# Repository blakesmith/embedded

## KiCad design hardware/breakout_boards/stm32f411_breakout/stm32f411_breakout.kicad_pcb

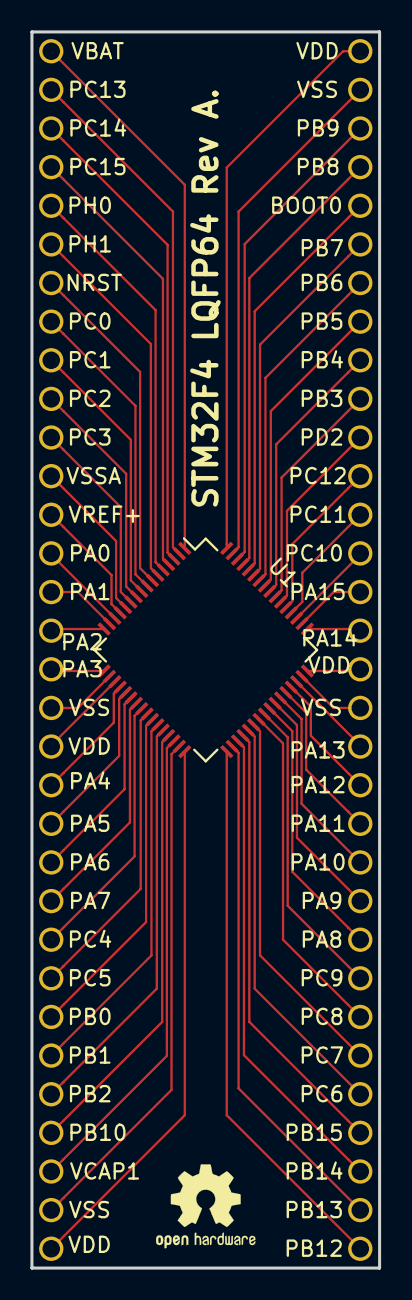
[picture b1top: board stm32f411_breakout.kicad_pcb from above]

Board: 2 copper layers, 22.9 x 81.3 mm, 65 parts (0 on the bottom side), 63 nets.

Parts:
BOOT0: Conn; Conn_1pin_2.54mm
NRST: Conn; Conn_1pin_2.54mm
PA0, PA1, PA2, PA3, PA4, PA5, PA6, PA7, PA8, PA9, PA10, PA11, PA12, PA13, PA14, PA15: Conn; Conn_1pin_2.54mm
PB0, PB1, PB2, PB3, PB4, PB5, PB6, PB7, PB8, PB9, PB10, PB12, PB13, PB14, PB15: Conn; Conn_1pin_2.54mm
PC0, PC1, PC2, PC3, PC4, PC5, PC6, PC7, PC8, PC9, PC10, PC11, PC12, PC13, PC14, PC15: Conn; Conn_1pin_2.54mm
PD2: Conn; Conn_1pin_2.54mm
PH0, PH1: Conn; Conn_1pin_2.54mm
U1: STM32F411RETx; LQFP-64_10x10mm_Pitch0.5mm
VBAT: Conn; Conn_1pin_2.54mm
VCAP1: Conn; Conn_1pin_2.54mm
VDD: Conn; Conn_1pin_2.54mm
VDD#2, VDD#3, VDD#4: Conn; Conn_1pin_2.54mm
VREF+: Conn; Conn_1pin_2.54mm
VSS: Conn; Conn_1pin_2.54mm
VSS#2, VSS#3, VSS#4: Conn; Conn_1pin_2.54mm
VSSA: Conn; Conn_1pin_2.54mm

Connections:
unnamed: NRST.1, U1.7
unnamed: BOOT0.1, U1.60
unnamed: U1.1, VBAT.1
unnamed: U1.13, VREF+.1
unnamed: U1.30, VCAP1.1
unnamed: PH0.1, U1.5
unnamed: PH1.1, U1.6
unnamed: PD2.1, U1.54
unnamed: PC0.1, U1.8
unnamed: PC1.1, U1.9
unnamed: PC2.1, U1.10
unnamed: PC3.1, U1.11
unnamed: PC4.1, U1.24
unnamed: PC5.1, U1.25
unnamed: PC6.1, U1.37
unnamed: PC7.1, U1.38
unnamed: PC8.1, U1.39
unnamed: PC9.1, U1.40
unnamed: PC10.1, U1.51
unnamed: PC11.1, U1.52
unnamed: PC12.1, U1.53
unnamed: PC13.1, U1.2
unnamed: PC15.1, U1.4
unnamed: U1.19, VDD.1
unnamed: U1.18, VSS.1
unnamed: U1.32, VDD#2.1
unnamed: U1.31, VSS#2.1
unnamed: U1.48, VDD#3.1
unnamed: U1.47, VSS#3.1
unnamed: U1.64, VDD#4.1
unnamed: U1.63, VSS#4.1
unnamed: U1.12, VSSA.1
unnamed: PA0.1, U1.14
unnamed: PA1.1, U1.15
unnamed: PA2.1, U1.16
unnamed: PA3.1, U1.17
unnamed: PA4.1, U1.20
unnamed: PA5.1, U1.21
unnamed: PA6.1, U1.22
unnamed: PA7.1, U1.23
unnamed: PA8.1, U1.41
unnamed: PA9.1, U1.42
unnamed: PA10.1, U1.43
unnamed: PA11.1, U1.44
unnamed: PA12.1, U1.45
unnamed: PA13.1, U1.46
unnamed: PA14.1, U1.49
unnamed: PA15.1, U1.50
unnamed: PB0.1, U1.26
unnamed: PB1.1, U1.27
unnamed: PB2.1, U1.28
unnamed: PB3.1, U1.55
unnamed: PB4.1, U1.56
unnamed: PB5.1, U1.57
unnamed: PB6.1, U1.58
unnamed: PB7.1, U1.59
unnamed: PB8.1, U1.61
unnamed: PB9.1, U1.62
unnamed: PB10.1, U1.29
unnamed: PB12.1, U1.33
unnamed: PB13.1, U1.34
unnamed: PB14.1, U1.35
unnamed: PB15.1, U1.36

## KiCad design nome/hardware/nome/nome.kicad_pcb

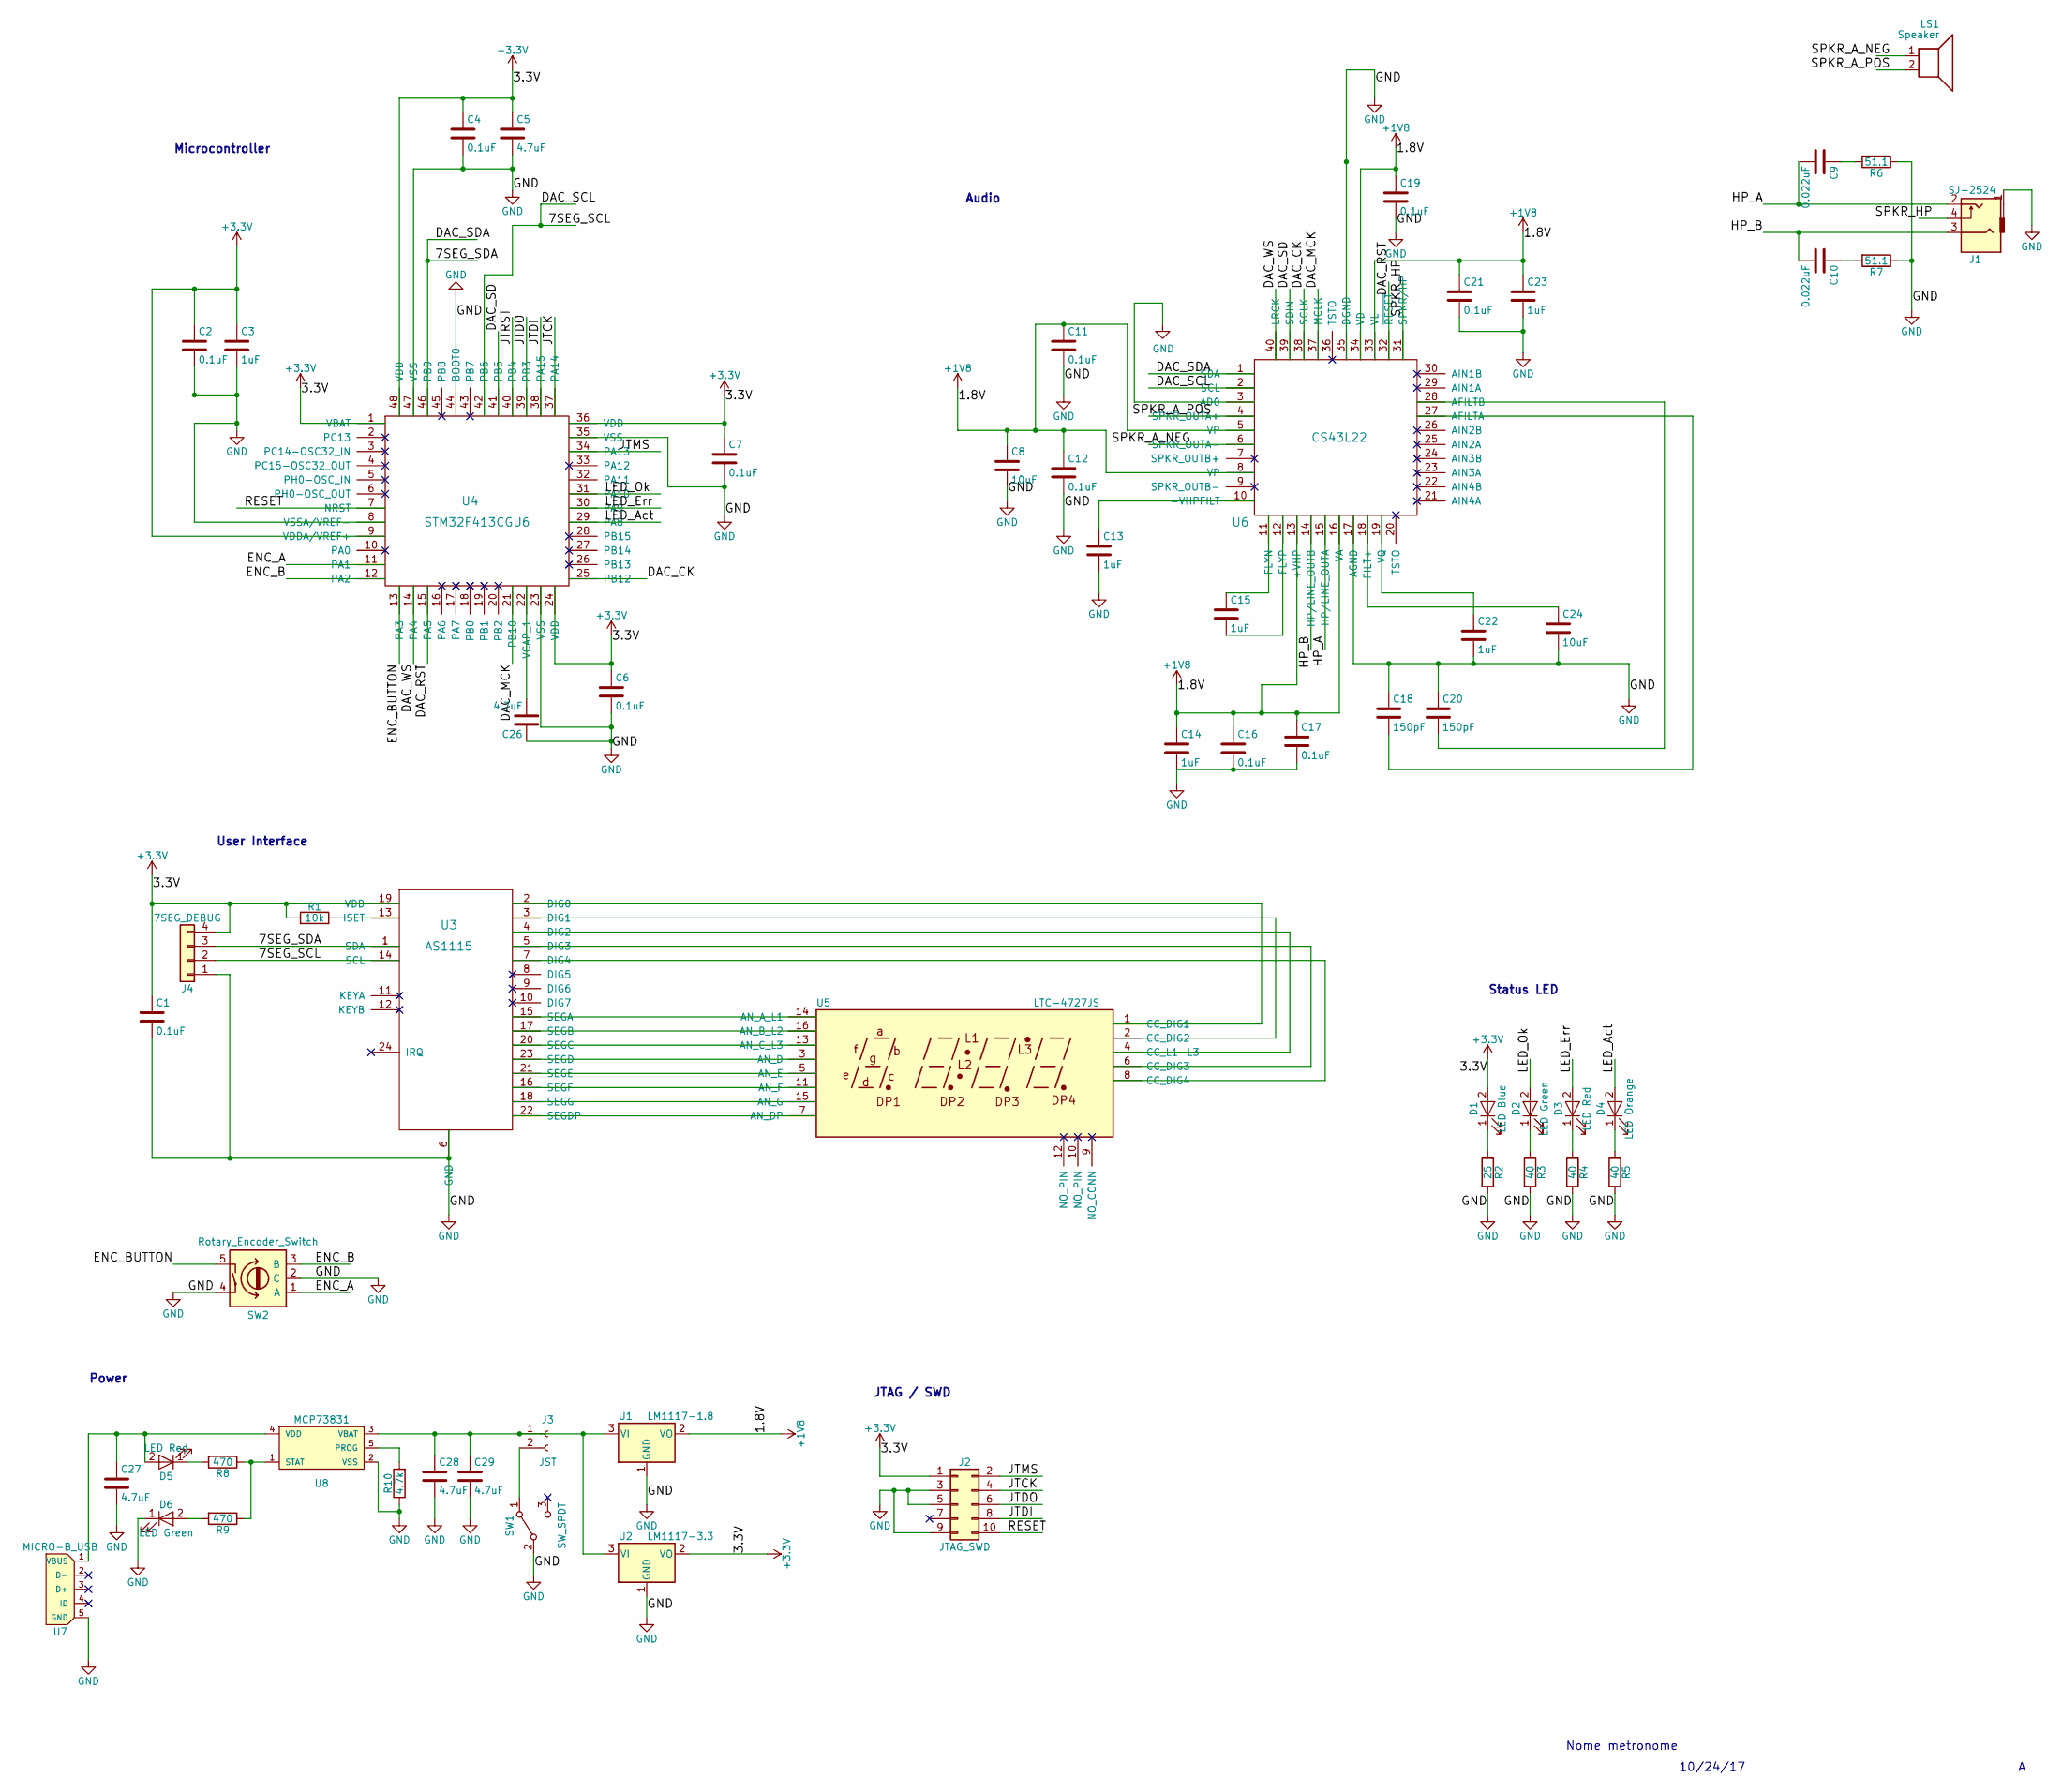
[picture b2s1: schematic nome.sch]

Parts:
C1, C2, C4, C6, C7, C11, C12, C16, C17, C19, C21: 0.1uF; C_0805_HandSoldering
C3, C13, C14, C15, C22, C23: 1uF; C_0805_HandSoldering
C5, C26, C27, C28, C29: 4.7uF; C_0805_HandSoldering
C8, C24: 10uF; C_0805_HandSoldering
C9, C10: 0.022uF; C_0805_HandSoldering
C18, C20: 150pF; C_0805_HandSoldering
D1: LED Blue; LED_0805_HandSoldering
D2, D6: LED Green; LED_0805_HandSoldering
D3, D5: LED Red; LED_0805_HandSoldering
D4: LED Orange; LED_0805_HandSoldering
J1: SJ-2524
J2: JTAG_SWD; Pin_Header_Straight_2x05_Pitch2.54mm
J3: JST; JST_PH_B2B-PH-SM4-TB_02x2.00mm_Straight
J4: 7SEG_DEBUG; Pin_Header_Straight_1x04_Pitch2.54mm
LS1: Speaker; WirePad-1x2-2.54mm
R1: 10k; R_0805_HandSoldering
R2: 25; R_0805_HandSoldering
R3, R4, R5: 40; R_0805_HandSoldering
R6, R7: 51.1; R_0805_HandSoldering
R8, R9: 470; R_0805_HandSoldering
R10: 4.7k; R_0805_HandSoldering
SW1: SW_SPDT; CK_SPDT
SW2: Rotary_Encoder_Switch; PEC11
U1: LM1117-1.8; SOT-223
U2: LM1117-3.3; SOT-223
U3: AS1115; QSOP-24_3.9x8.7mm_Pitch0.635mm
U4: STM32F413CGU6; LQFP-48_7x7mm_Pitch0.5mm
U5: LTC-4727JS; LTC-4727
U6: CS43L22; QFN-40-1EP_6x6mm_Pitch0.5mm
U7: MICRO-B_USB
U8: MCP73831; SOT-23-5_HandSoldering

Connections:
+1V8: C8.1, C11.1, C12.1, C14.1, C16.1, C17.1, C19.1, C21.1, C23.1, U1.2 (VO), U6.5 (VP), U6.8 (VP), U6.13 (+VHP), U6.16 (VA), U6.33 (VL), U6.34 (VD)
+3V3: C1.1, C2.1, C3.1, C4.1, C5.1, C6.1, C7.1, D1.2 (A), J2.1, J4.4, R1.1, U2.2 (VO), U3.19 (VDD), U4.1 (VBAT), U4.9 (VDDA/VREF+), U4.24 (VDD), U4.36 (VDD), U4.48 (VDD)
/7SEG_SCL: J4.2, U3.14 (SCL), U4.42 (PB6), U6.2 (SCL)
/7SEG_SDA: J4.3, U3.1 (SDA), U4.46 (PB9), U6.1 (SDA)
/DAC_CK: U4.25 (PB12), U6.38 (SCLK)
/DAC_MCK: U4.21 (PB10), U6.37 (MCLK)
/DAC_RST: U4.15 (PA5), U6.32 (~RESET)
/DAC_SD: U4.41 (PB5), U6.39 (SDIN)
/DAC_WS: U4.14 (PA4), U6.40 (LRCK)
/ENC_A: SW2.1 (A), U4.11 (PA1)
/ENC_B: SW2.3 (B), U4.12 (PA2)
/ENC_BUTTON: SW2.5, U4.13 (PA3)
/HP_A: C9.2, J1.2, U6.15 (HP/LINE_OUTA)
/HP_B: C10.2, J1.3, U6.14 (HP/LINE_OUTB)
/JTCK: J2.4, U4.37 (PA14)
/JTDI: J2.8, U4.38 (PA15)
/JTDO: J2.6, U4.39 (PB3)
/JTMS: J2.2, U4.34 (PA13)
/JTRST: U4.40 (PB4)
/LED_Act: D4.2 (A), U4.29 (PA8)
/LED_Err: D3.2 (A), U4.30 (PA9)
/LED_Ok: D2.2 (A), U4.31 (PA10)
/RESET: J2.10, U4.7 (NRST)
/SPKR_A_NEG: LS1.1, U6.6 (SPKR_OUTA-)
/SPKR_A_POS: LS1.2, U6.4 (SPKR_OUTA+)
/SPKR_HP: J1.4, U6.31 (SPKR/HP)
GND: C1.2, C2.2, C3.2, C4.2, C5.2, C6.2, C7.2, C8.2, C11.2, C12.2, C13.2, C14.2, C16.2, C17.2, C18.1, C19.2, C20.1, C21.2, C22.2, C23.2, C24.2, C26.1, C27.2, C28.2, C29.2, D6.1 (K), J1.1, J2.3, J2.5, J2.9, J4.1, R2.2, R3.2, R4.2, R5.2, R6.1, R7.1, R10.1, SW1.2 (B), SW2.2 (C), SW2.4, U1.1 (GND), U2.1 (GND), U3.6 (GND), U4.8 (VSSA/VREF-), U4.23 (VSS), U4.35 (VSS), U4.44 (BOOT0), U4.47 (VSS), U6.3 (AD0), U6.17 (AGND), U6.35 (DGND), U7.5 (GND), U8.2 (VSS)
unnamed: C9.1, R6.2
unnamed: C10.1, R7.2
unnamed: C13.1, U6.10 (-VHPFILT)
unnamed: C15.1, U6.11 (FLYN)
unnamed: C15.2, U6.12 (FLYP)
unnamed: C18.2, U6.27 (AFILTA)
unnamed: C20.2, U6.28 (AFILTB)
unnamed: C22.1, U6.19 (VQ)
unnamed: C24.1, U6.18 (FILT+)
unnamed: C26.2, U4.22 (VCAP_1)
unnamed: C27.1, D5.2 (A), U7.1 (VBUS), U8.4 (VDD)
unnamed: C28.1, C29.1, J3.1, U1.3 (VI), U2.3 (VI), U8.3 (VBAT)
unnamed: D1.1 (K), R2.1
unnamed: D2.1 (K), R3.1
unnamed: D3.1 (K), R4.1
unnamed: D4.1 (K), R5.1
unnamed: D5.1 (K), R8.2
unnamed: D6.2 (A), R9.2
unnamed: J3.2, SW1.1 (A)
unnamed: R1.2, U3.13 (ISET)
unnamed: R8.1, R9.1, U8.1 (STAT)
unnamed: R10.2, U8.5 (PROG)
unnamed: U3.2 (DIG0), U5.1 (CC_DIG1)
unnamed: U3.3 (DIG1), U5.2 (CC_DIG2)
unnamed: U3.4 (DIG2), U5.4 (CC_L1-L3)
unnamed: U3.5 (DIG3), U5.6 (CC_DIG3)
unnamed: U3.7 (DIG4), U5.8 (CC_DIG4)
unnamed: U3.15 (SEGA), U5.14 (AN_A_L1)
unnamed: U3.16 (SEGF), U5.11 (AN_F)
unnamed: U3.17 (SEGB), U5.16 (AN_B_L2)
unnamed: U3.18 (SEGG), U5.15 (AN_G)
unnamed: U3.20 (SEGC), U5.13 (AN_C_L3)
unnamed: U3.21 (SEGE), U5.5 (AN_E)
unnamed: U3.22 (SEGDP), U5.7 (AN_DP)
unnamed: U3.23 (SEGD), U5.3 (AN_D)

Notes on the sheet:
User Interface
Power
JTAG / SWD
Status LED
Audio
Microcontroller
Nome metronome
10/24/17

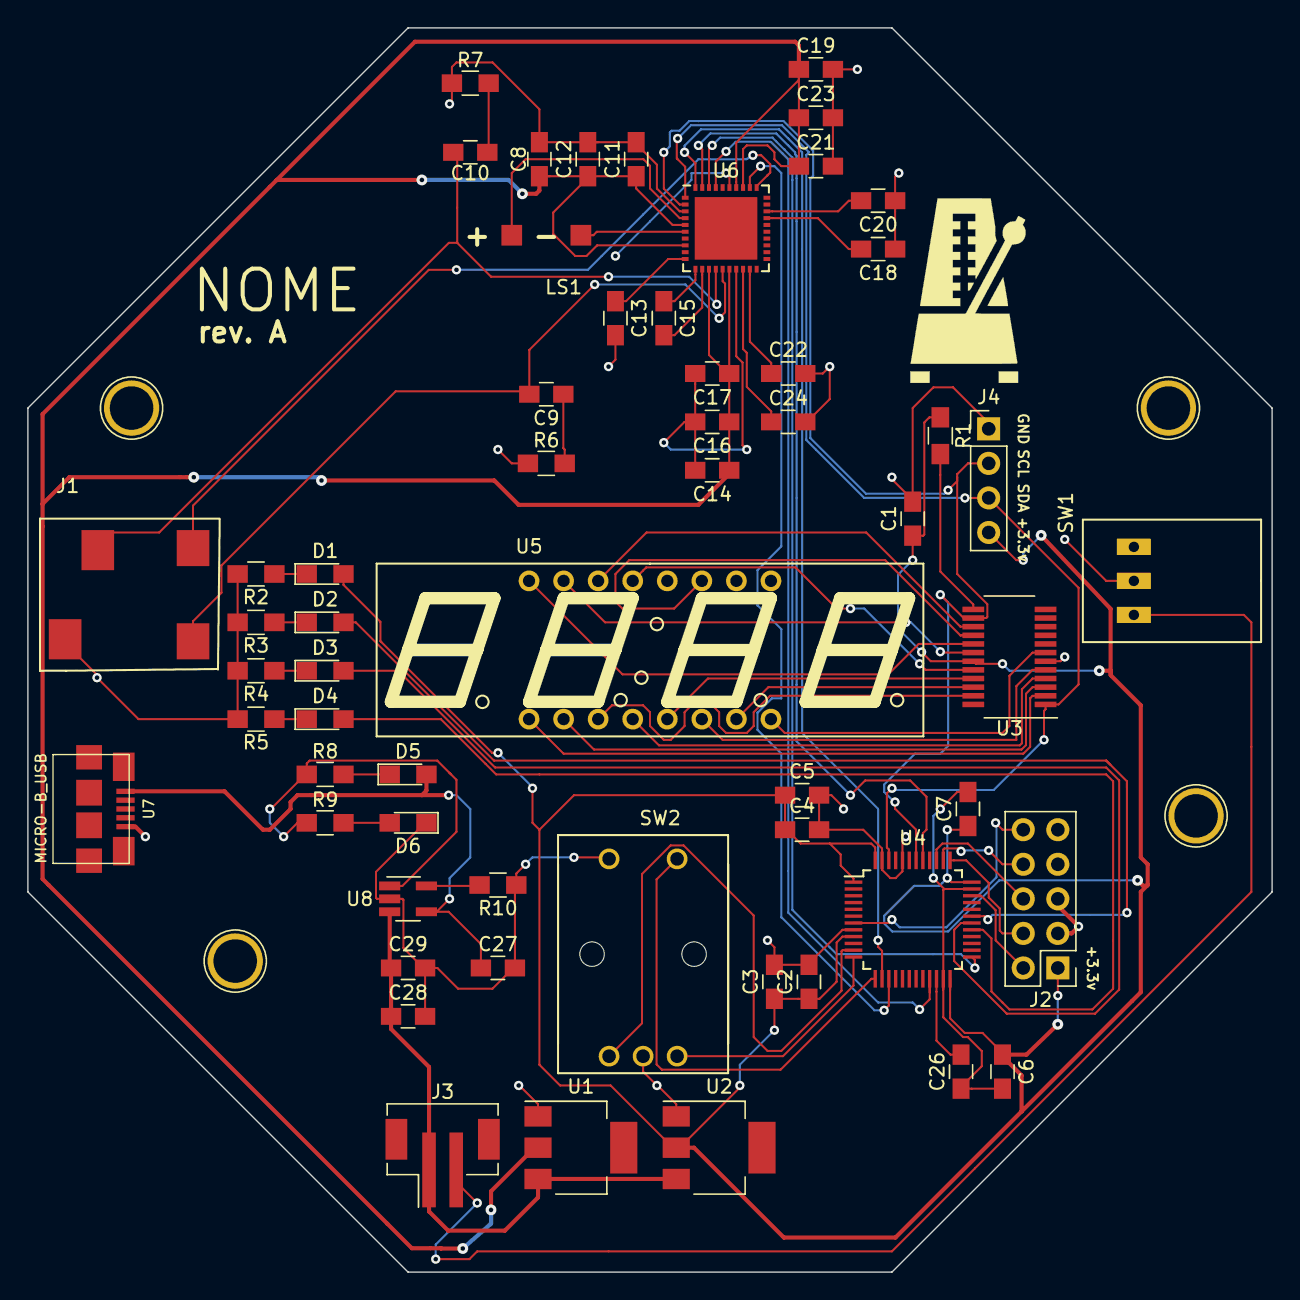
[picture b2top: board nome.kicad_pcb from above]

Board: 2 copper layers, 91.4 x 91.4 mm, 59 parts (0 on the bottom side), 61 nets.

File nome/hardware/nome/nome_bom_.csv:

Component,Description,Part,References,Value,Footprint,Quantity Per PCB,Datasheet,S1PL,MFP,MFN,S1PN
1,Unpolarized capacitor,C,C9 C10,0.022uF,C_0805_HandSoldering,2,http://datasheets.avx.com/X7RDielectric.pdf,https://www.digikey.com/product-detail/en/avx-corporation/08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,08051C223KAT2A,AVX Corporation,478-1360-1-ND
2,Unpolarized capacitor,C,C1 C2 C4 C6 C7 C11 C12 C16 C17 C19 C21,0.1uF,C_0805_HandSoldering,11,http://datasheets.avx.com/X7RDielectric.pdf,https://www.digikey.com/product-detail/en/avx-corporation/08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,08055C104KAT2A,AVX Corporation,478-1395-1-ND
3,Unpolarized capacitor,C,C8 C24,10uF,C_0805_HandSoldering,2,http://datasheets.avx.com/cx5r.pdf,https://www.digikey.com/product-detail/en/avx-corporation/08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,0805ZD106KAT2A,AVX Corporation,478-5167-1-ND
4,Unpolarized capacitor,C,C18 C20,150pF,C_0805_HandSoldering,2,http://datasheets.avx.com/C0GNP0-Dielectric.pdf,https://www.digikey.com/product-detail/en/avx-corporation/08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,08055A151JAT2A,AVX Corporation,478-1318-1-ND
5,Unpolarized capacitor,C,C3 C13 C14 C15 C22 C23,1uF,C_0805_HandSoldering,6,http://datasheets.avx.com/X7RDielectric.pdf,https://www.digikey.com/product-detail/en/avx-corporation/08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,0805ZC105KAT2A,AVX Corporation,478-1405-1-ND
6,Unpolarized capacitor,C,C5 C26 C27 C28 C29,4.7uF,C_0805_HandSoldering,5,http://datasheets.avx.com/cx5r.pdf,https://www.digikey.com/product-detail/en/avx-corporation/08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,0805ZD475KAT2A,AVX Corporation,478-1415-1-ND
7,LED generic,LED,D1,LED Blue,LED_0805_HandSoldering,1,http://optoelectronics.liteon.com/upload/download/DS22-2000-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,https://www.digikey.com/product-detail/en/lite-on-inc/LTST-C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,LTST-C171TBKT,Lite-On Inc.,160-1645-1-ND
8,LED generic,LED,D2 D6,LED Green,LED_0805_HandSoldering,2,https://media.digikey.com/pdf/Data%20Sheets/Lite-On%20PDFs/L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,https://www.digikey.com/product-detail/en/lite-on-inc/LTST-C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,LTST-C171GKT,Lite-On Inc.,160-1423-1-ND
9,LED generic,LED,D4,LED Orange,LED_0805_HandSoldering,1,http://optoelectronics.liteon.com/upload/download/DS-22-99-0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,https://www.digikey.com/product-detail/en/lite-on-inc/LTST-C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,LTST-C171AKT,Lite-On Inc.,160-1419-1-ND
10,LED generic,LED,D3 D5,LED Red,LED_0805_HandSoldering,2,http://optoelectronics.liteon.com/upload/download/DS22-2000-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,https://www.digikey.com/product-detail/en/lite-on-inc/LTST-C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,LTST-C171KRK,Lite-On Inc.,160-1427-1-ND
11,,Conn_01x04,J4,7SEG_DEBUG,Pin_Header_Straight_1x04_Pitch2.54mm,1,https://cdn.harwin.com/pdfs/Harwin_Product_Catalog_page_208.pdf,https://www.digikey.com/product-detail/en/harwin-inc/M20-999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,M20-9990445,Harwin Inc.,952-2265-ND
12,,Conn_01x02_Female,J3,JST,JST_PH_B2B-PH-SM4-TB_02x2.00mm_Straight,1,http://www.jst-mfg.com/product/pdf/eng/ePH.pdf,https://www.digikey.com/product-detail/en/jst-sales-america-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,B2B-PH-SM4-TB(LF)(SN),JST Sales America Inc.,455-1734-1-ND
13,,Conn_02x05_Odd_Even,J2,JTAG_SWD,Pin_Header_Straight_2x05_Pitch2.54mm,1,http://www.on-shore.com/wp-content/uploads/2015/09/302-sxxx.pdf,https://www.digikey.com/product-detail/en/on-shore-technolog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,302-S101,On Shore Technology Inc.,ED1543-ND
14,3-pin audio jack receptable (stereo/TRS connector) with 2 switching contacts,SJ-2524,J1,SJ-2524,SJ-2524,1,http://www.cui.com/product/resource/sj-252x-smt-series.pdf,https://www.digikey.com/product-detail/en/cui-inc/SJ-2524-SM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,SJ-2524-SMT-TR,CUI Inc.,CP-2524SJCT-ND
15,speaker,Speaker,LS1,Speaker,WirePad-1x2-2.54mm,1,https://media.digikey.com/pdf/Data%20Sheets/Mallory%20Sonale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,https://www.digikey.com/product-detail/en/mallory-sonalert-p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,PSR-57N08A01-AQ,Mallory Sonalert Products Inc.,458-1136-ND
16,Resistor,R,R1,10k,R_0805_HandSoldering,1,http://www.yageo.com.tw/exep/pages/download/literatures/PYu-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,https://www.digikey.com/product-detail/en/yageo/RC0805JR-071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,RC0805JR-0710KL,Yageo,311-10KARCT-ND
17,Resistor,R,R2,25,R_0805_HandSoldering,1,http://www.yageo.com.tw/exep/pages/download/literatures/PYu-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,https://www.digikey.com/product-detail/en/yageo/RC0805FR-072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,RC0805FR-0724R9L,Yageo,311-24.9CRCT-ND
18,Resistor,R,R10,4.7k,R_0805_HandSoldering,1,http://www.yageo.com.tw/exep/pages/download/literatures/PYu-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,https://www.digikey.com/product-detail/en/yageo/RC0805FR-074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,RC0805FR-074K7L,Yageo,311-4.70KCRCT-ND
19,Resistor,R,R3 R4 R5,40,R_0805_HandSoldering,3,http://www.yageo.com.tw/exep/pages/download/literatures/PYu-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,https://www.digikey.com/product-detail/en/yageo/RC0805FR-074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,RC0805FR-0740R2L,Yageo,311-40.2CRCT-ND
20,Resistor,R,R8 R9,470,R_0805_HandSoldering,2,http://www.yageo.com.tw/exep/pages/download/literatures/PYu-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,https://www.digikey.com/product-detail/en/yageo/RC0805JR-074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,RC0805JR-07470RL,Yageo,311-470ARCT-ND
21,Resistor,R,R6 R7,51.1,R_0805_HandSoldering,2,http://www.yageo.com.tw/exep/pages/download/literatures/PYu-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,https://www.digikey.com/product-detail/en/yageo/RC0805FR-075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,RC0805FR-0751R1L,Yageo,311-51.1CRCT-ND
22,"Rotary encoder, dual channel, incremental quadrate outputs, with switch",Rotary_Encoder_Switch,SW2,Rotary_Encoder_Switch,PEC11,1,http://www.bourns.com/docs/Product-Datasheets/PEC11R.pdf,https://www.digikey.com/product-detail/en/bourns-inc/PEC11R-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,PEC11R-4215K-S0024,Bourns Inc.,PEC11R-4215K-S0024-ND
23,,SW_SPDT,SW1,SW_SPDT,CK_SPDT,1,http://www.ckswitches.com/media/1422/js.pdf,https://www.digikey.com/product-detail/en/c-k/JS102011SAQN/4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,JS102011SAQN,C&K,401-1999-1-ND
24,,AS1115,U3,AS1115,QSOP-24_3.9x8.7mm_Pitch0.635mm,1,http://ams.com/eng/content/download/18430/343782,https://www.digikey.com/product-detail/en/ams/AS1115-BSST/AS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,AS1115-BSST,ams,AS1115-BSSTCT-ND
25,,CS43L22,U6,CS43L22,QFN-40-1EP_6x6mm_Pitch0.5mm,1,https://d3uzseaevmutz1.cloudfront.net/pubs/proDatasheet/CS43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,https://www.digikey.com/product-detail/en/cirrus-logic-inc/C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,CS43L22-CNZ,Cirrus Logic Inc.,598-1650-ND
26,"800mA Low-Dropout Linear Regulator, 1.8V fixed output, TO-220/TO-252/TO-263/SOT-223",LM1117-1.8,U1,LM1117-1.8,SOT-223,1,http://www.st.com/content/ccc/resource/technical/document/da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,https://www.digikey.com/product-detail/en/stmicroelectronics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,LD1117S18TR,STMicroelectronics,497-7308-1-ND
27,"800mA Low-Dropout Linear Regulator, 1.8V fixed output, TO-220/TO-252/TO-263/SOT-223",LM1117-3.3,U2,LM1117-3.3,SOT-223,1,http://www.st.com/content/ccc/resource/technical/document/da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,https://www.digikey.com/product-detail/en/stmicroelectronics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,LD1117S33TR,STMicroelectronics,497-1242-6-ND
28,"4 digit 7 segment Green LED, common anode",LTC-4727JS,U5,LTC-4727JS,LTC-4727,1,https://media.digikey.com/pdf/Data%20Sheets/Lite-On%20PDFs/L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,https://www.digikey.com/product-detail/en/lite-on-inc/LTC-47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,LTC-4727JS,Lite-On Inc.,160-1547-5-ND
29,Li-Polymer Charge Management Controller,MCP73831,U8,MCP73831,SOT-23-5_HandSoldering,1,http://ww1.microchip.com/downloads/en/DeviceDoc/20001060AQ.pdf,https://www.digikey.com/product-detail/en/microchip-technolo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,MCP73831T-2ACI/OT,Microchip Technology,MCP73831T-2ACI/OTCT-ND
30,Micro-B USB connector,MICRO-B_USB,U7,MICRO-B_USB,MICRO-B_USB,1,http://portal.fciconnect.com/Comergent/fci/drawing/10118192.pdf,https://www.digikey.com/product-detail/en/amphenol-fci/10118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,10118192-0001LF,Amphenol FCI,609-4613-1-ND
31,,STMF411CEU6,U4,STM32F413CGU6,LQFP-48_7x7mm_Pitch0.5mm,1,http://www.st.com/content/ccc/resource/technical/document/da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,https://www.digikey.com/product-detail/en/stmicroelectronics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,STM32F413CGU6,STMicroelectronics,497-17017-ND
